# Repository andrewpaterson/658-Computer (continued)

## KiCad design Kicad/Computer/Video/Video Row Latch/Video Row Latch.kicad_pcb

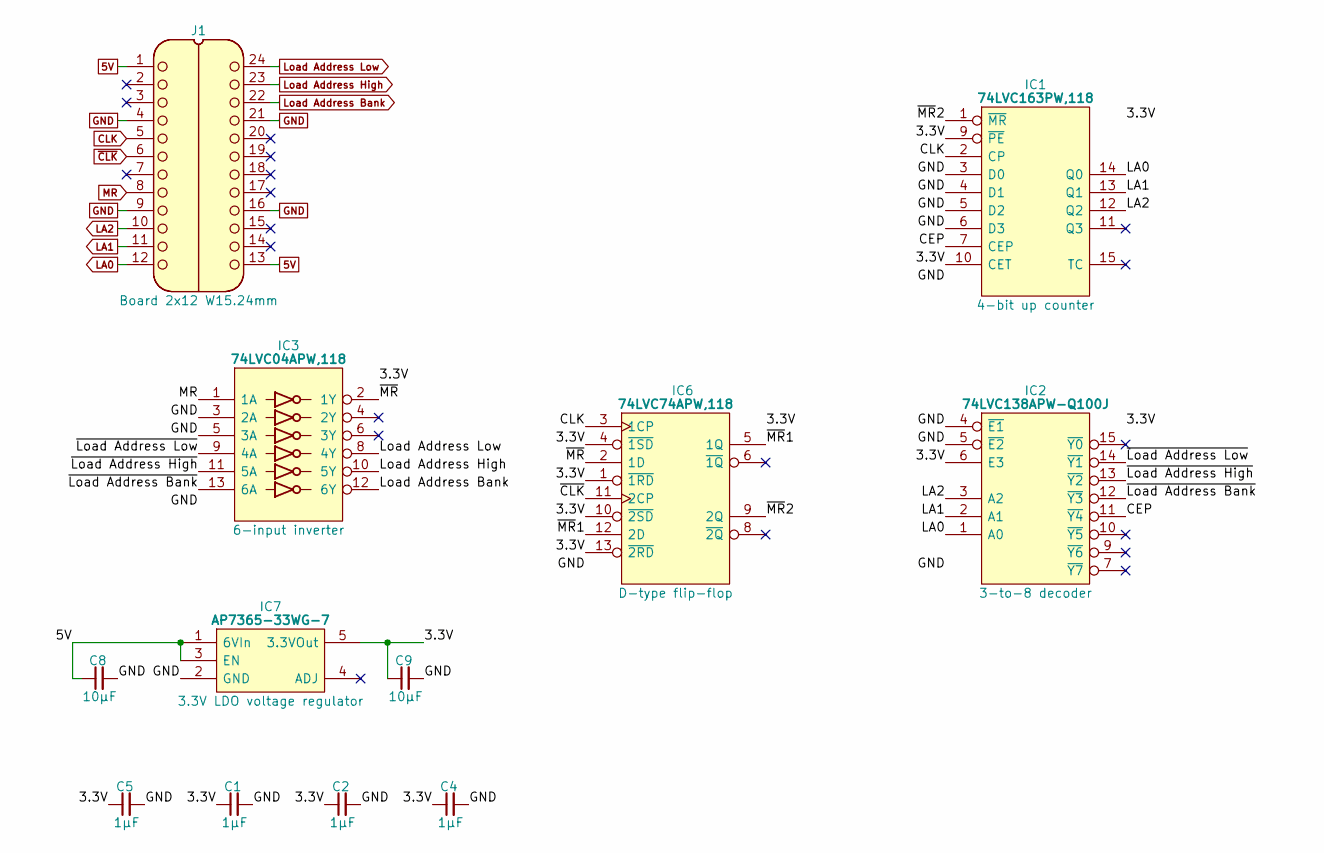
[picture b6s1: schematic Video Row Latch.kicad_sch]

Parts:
C1, C2, C4, C5: 1μF; C_0805
C8, C9: 10μF; C_0805
IC1: 74LVC163PW,118; SOP65P640X110-16N; Mouser Part Number 771-74LVC163PW-T
IC2: 74LVC138APW-Q100J; SOP65P640X110-16N; Mouser Part Number 771-74LVC138APWQ100J
IC3: 74LVC04APW,118; SOP65P640X110-14N; Manufacturer_Part_Number 74LVC04APW,118; Mouser Part Number 771-74LVC04APW-T
IC6: 74LVC74APW,118; SOP65P640X110-14N; Mouser Part Number 771-74LVC74APW-T
IC7: AP7365-33WG-7; SOT95P285X130-5N; Manufacturer_Part_Number AP7365-33WG-7; Mouser Part Number 621-AP7365-33WG-7
J1: Board 2x12 W15.24mm; DIP-24_Board_W15.24mm

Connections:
5V: C8.1, IC7.1 (6VIn), IC7.3 (EN), J1.1, J1.13
/3.3V: C1.1, C2.1, C4.1, C5.1, C9.1, IC1.9 (~PE), IC1.10 (CET), IC1.16 (3V), IC2.6 (E3), IC2.16 (3V), IC3.14 (3V), IC6.1 (~1RD), IC6.4 (~1SD), IC6.10 (~2SD), IC6.13 (~2RD), IC6.14 (3V), IC7.5 (3.3VOut)
/CEP: IC1.7 (CEP), IC2.11 (~Y4)
/~Load Address Bank: IC2.12 (~Y3), IC3.13 (6A)
/~Load Address High: IC2.13 (~Y2), IC3.11 (5A)
/~Load Address Low: IC2.14 (~Y1), IC3.9 (4A)
/~MR: IC3.2 (1Y), IC6.2 (1D)
/~MR1: IC6.5 (1Q), IC6.12 (2D)
/~MR2: IC1.1 (~MR), IC6.9 (2Q)
CLK: IC1.2 (CP), IC6.3 (1CP), J1.5
GND: C1.2, C2.2, C4.2, C5.2, C8.2, C9.2, IC1.3 (D0), IC1.4 (D1), IC1.5 (D2), IC1.6 (D3), IC1.8 (GND), IC2.4 (~E1), IC2.5 (~E2), IC2.8 (GND), IC3.3 (2A), IC3.5 (3A), IC3.7 (GND), IC6.7 (GND), IC7.2 (GND), J1.4, J1.9, J1.16, J1.21
LA0: IC1.14 (Q0), IC2.1 (A0), J1.12
LA1: IC1.13 (Q1), IC2.2 (A1), J1.11
LA2: IC1.12 (Q2), IC2.3 (A2), J1.10
Load Address Bank: IC3.12 (6Y), J1.22
Load Address High: IC3.10 (5Y), J1.23
Load Address Low: IC3.8 (4Y), J1.24
MR: IC3.1 (1A), J1.8
~CLK: IC6.11 (2CP), J1.6

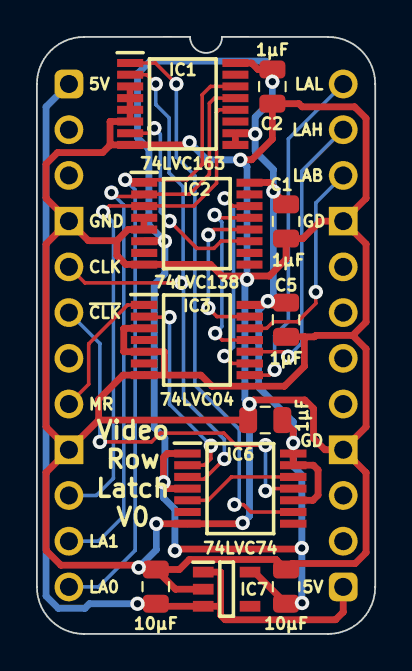
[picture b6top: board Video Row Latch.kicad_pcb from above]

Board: 2 copper layers, 18.8 x 33.2 mm, 12 parts (0 on the bottom side), 19 nets.

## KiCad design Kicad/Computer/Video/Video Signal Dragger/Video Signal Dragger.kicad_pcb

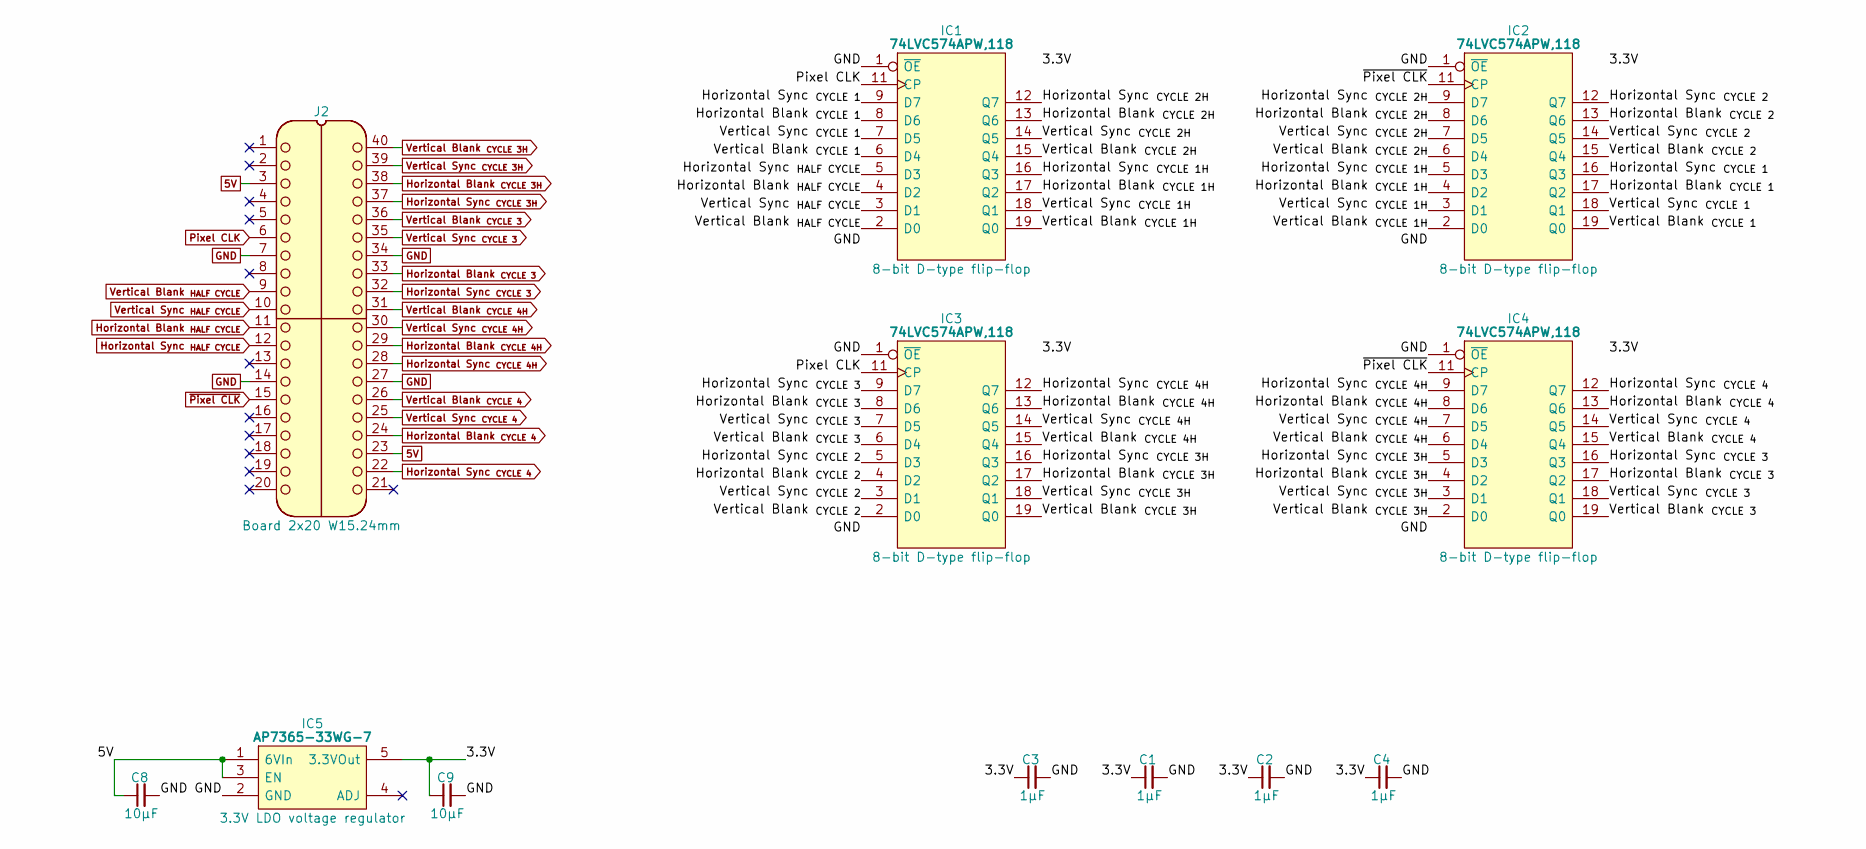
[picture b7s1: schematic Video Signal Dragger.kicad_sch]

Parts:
C1, C2, C3, C4: 1μF; C_0805
C8, C9: 10µF; C_0805
IC1, IC2, IC3, IC4: 74LVC574APW,118; SOP65P640X110-20N; Manufacturer_Part_Number 74LVC574APW,118; Mouser Part Number 771-74LVC574APW-T
IC5: AP7365-33WG-7; SOT95P285X130-5N; Manufacturer_Part_Number AP7365-33WG-7; Mouser Part Number 621-AP7365-33WG-7
J2: Board 2x20 W15.24mm; DIP-40_Board_W15.24mm

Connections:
5V: C8.1, IC5.1 (6VIn), IC5.3 (EN), J2.3, J2.23
/3.3V: C1.1, C2.1, C3.1, C4.1, C9.1, IC1.20 (3V), IC2.20 (3V), IC3.20 (3V), IC4.20 (3V), IC5.5 (3.3VOut)
/Horizontal Blank _{CYCLE 1H}: IC1.17 (Q2), IC2.4 (D2)
/Horizontal Blank _{CYCLE 1}: IC1.8 (D6), IC2.17 (Q2)
/Horizontal Blank _{CYCLE 2H}: IC1.13 (Q6), IC2.8 (D6)
/Horizontal Blank _{CYCLE 2}: IC2.13 (Q6), IC3.4 (D2)
/Horizontal Sync _{CYCLE 1H}: IC1.16 (Q3), IC2.5 (D3)
/Horizontal Sync _{CYCLE 1}: IC1.9 (D7), IC2.16 (Q3)
/Horizontal Sync _{CYCLE 2H}: IC1.12 (Q7), IC2.9 (D7)
/Horizontal Sync _{CYCLE 2}: IC2.12 (Q7), IC3.5 (D3)
/Vertical Blank _{CYCLE 1H}: IC1.19 (Q0), IC2.2 (D0)
/Vertical Blank _{CYCLE 1}: IC1.6 (D4), IC2.19 (Q0)
/Vertical Blank _{CYCLE 2H}: IC1.15 (Q4), IC2.6 (D4)
/Vertical Blank _{CYCLE 2}: IC2.15 (Q4), IC3.2 (D0)
/Vertical Sync _{CYCLE 1H}: IC1.18 (Q1), IC2.3 (D1)
/Vertical Sync _{CYCLE 1}: IC1.7 (D5), IC2.18 (Q1)
/Vertical Sync _{CYCLE 2H}: IC1.14 (Q5), IC2.7 (D5)
/Vertical Sync _{CYCLE 2}: IC2.14 (Q5), IC3.3 (D1)
GND: C1.2, C2.2, C3.2, C4.2, C8.2, C9.2, IC1.1 (~OE), IC1.10 (GND), IC2.1 (~OE), IC2.10 (GND), IC3.1 (~OE), IC3.10 (GND), IC4.1 (~OE), IC4.10 (GND), IC5.2 (GND), J2.7, J2.14, J2.27, J2.34
Horizontal Blank _{CYCLE 3H}: IC3.17 (Q2), IC4.4 (D2), J2.38
Horizontal Blank _{CYCLE 3}: IC3.8 (D6), IC4.17 (Q2), J2.33
Horizontal Blank _{CYCLE 4H}: IC3.13 (Q6), IC4.8 (D6), J2.29
Horizontal Blank _{CYCLE 4}: IC4.13 (Q6), J2.24
Horizontal Blank _{HALF CYCLE}: IC1.4 (D2), J2.11
Horizontal Sync _{CYCLE 3H}: IC3.16 (Q3), IC4.5 (D3), J2.37
Horizontal Sync _{CYCLE 3}: IC3.9 (D7), IC4.16 (Q3), J2.32
Horizontal Sync _{CYCLE 4H}: IC3.12 (Q7), IC4.9 (D7), J2.28
Horizontal Sync _{CYCLE 4}: IC4.12 (Q7), J2.22
Horizontal Sync _{HALF CYCLE}: IC1.5 (D3), J2.12
Pixel CLK: IC1.11 (CP), IC3.11 (CP), J2.6
Vertical Blank _{CYCLE 3H}: IC3.19 (Q0), IC4.2 (D0), J2.40
Vertical Blank _{CYCLE 3}: IC3.6 (D4), IC4.19 (Q0), J2.36
Vertical Blank _{CYCLE 4H}: IC3.15 (Q4), IC4.6 (D4), J2.31
Vertical Blank _{CYCLE 4}: IC4.15 (Q4), J2.26
Vertical Blank _{HALF CYCLE}: IC1.2 (D0), J2.9
Vertical Sync _{CYCLE 3H}: IC3.18 (Q1), IC4.3 (D1), J2.39
Vertical Sync _{CYCLE 3}: IC3.7 (D5), IC4.18 (Q1), J2.35
Vertical Sync _{CYCLE 4H}: IC3.14 (Q5), IC4.7 (D5), J2.30
Vertical Sync _{CYCLE 4}: IC4.14 (Q5), J2.25
Vertical Sync _{HALF CYCLE}: IC1.3 (D1), J2.10
~Pixel CLK: IC2.11 (CP), IC4.11 (CP), J2.15

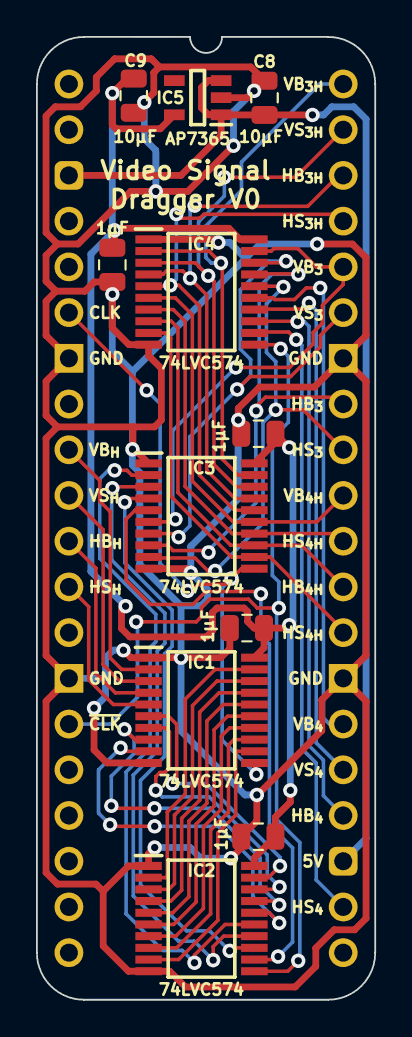
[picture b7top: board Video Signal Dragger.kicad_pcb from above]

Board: 2 copper layers, 18.8 x 53.5 mm, 12 parts (0 on the bottom side), 41 nets.

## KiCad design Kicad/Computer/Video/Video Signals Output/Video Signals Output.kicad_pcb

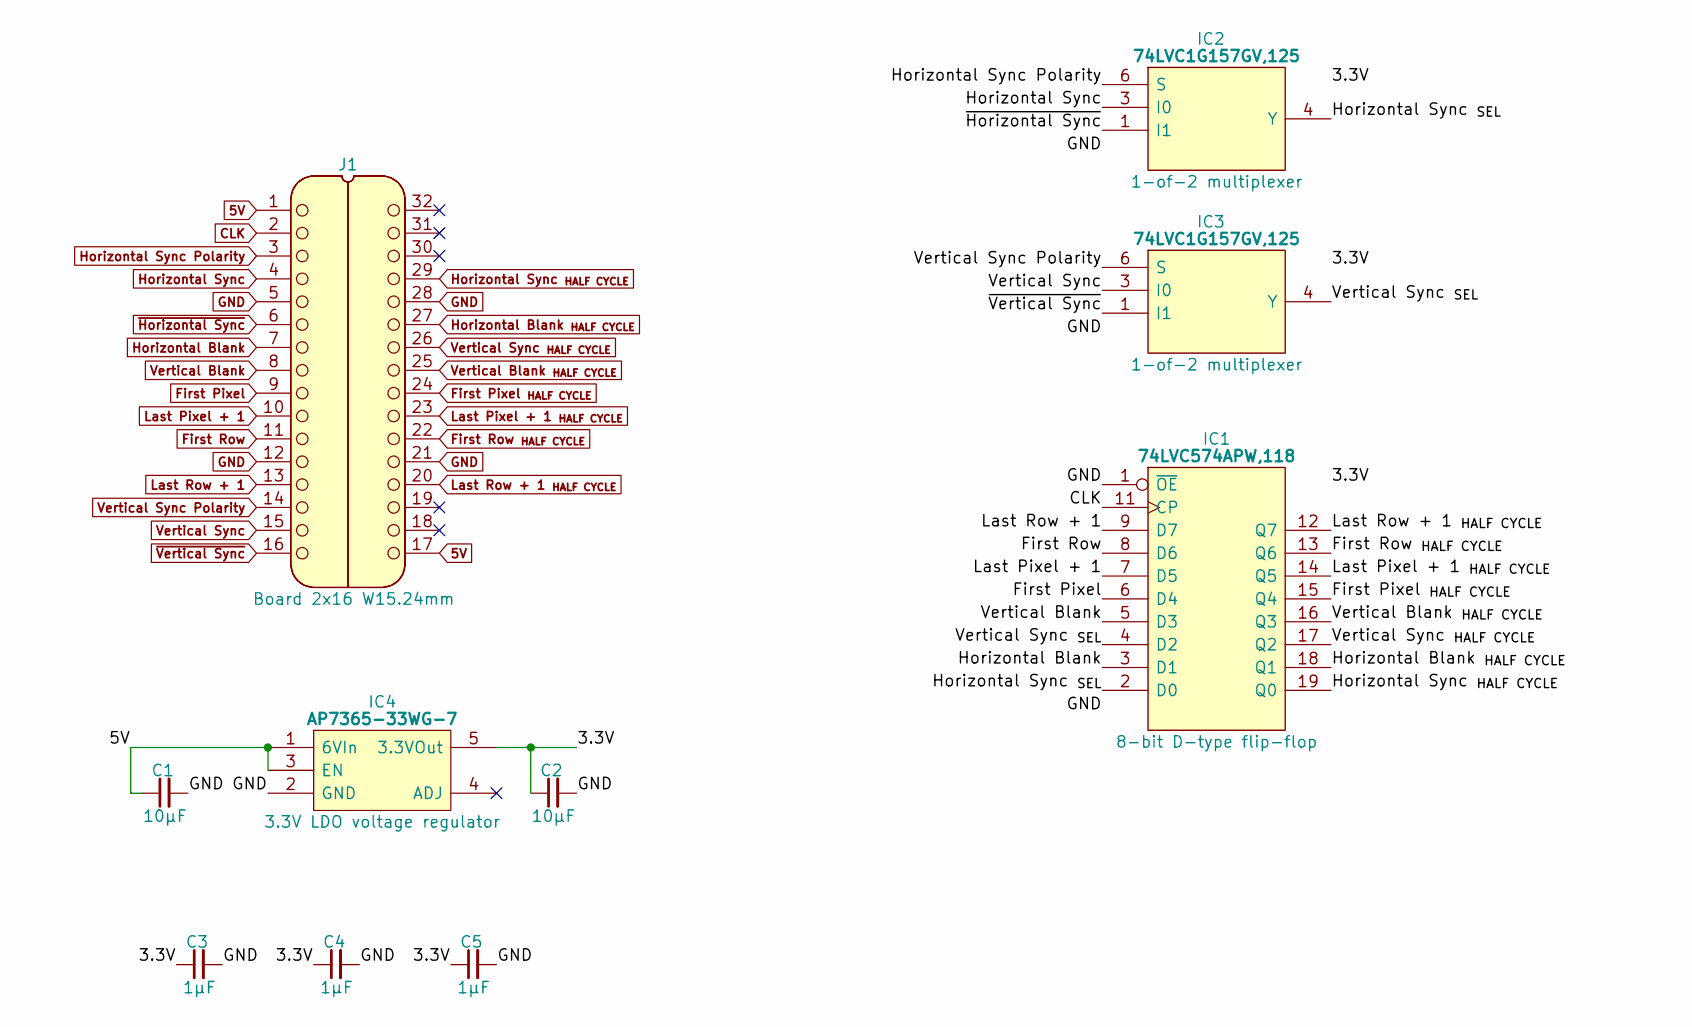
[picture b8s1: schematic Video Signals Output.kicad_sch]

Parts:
C1, C2: 10µF; C_0805
C3, C4, C5: 1μF; C_0805
IC1: 74LVC574APW,118; SOP65P640X110-20N; Manufacturer_Part_Number 74LVC574APW,118; Mouser Part Number 771-74LVC574APW-T
IC2, IC3: 74LVC1G157GV,125; 74LVC1G157GV125; Manufacturer_Part_Number 74LVC1G157GV,125; Mouser Part Number 771-74LVC1G157GV-G
IC4: AP7365-33WG-7; SOT95P285X130-5N; Manufacturer_Part_Number AP7365-33WG-7; Mouser Part Number 621-AP7365-33WG-7
J1: Board 2x16 W15.24mm; DIP-32_Board_W15.24mm

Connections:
5V: C1.1, IC4.1 (6VIn), IC4.3 (EN), J1.1, J1.17
/3.3V: C2.1, C3.1, C4.1, C5.1, IC1.20 (3V), IC2.5 (3V), IC3.5 (3V), IC4.5 (3.3VOut)
/Horizontal Sync _{SEL}: IC1.2 (D0), IC2.4 (Y)
/Vertical Sync _{SEL}: IC1.4 (D2), IC3.4 (Y)
CLK: IC1.11 (CP), J1.2
First Pixel: IC1.6 (D4), J1.9
First Pixel _{HALF CYCLE}: IC1.15 (Q4), J1.24
First Row: IC1.8 (D6), J1.11
First Row _{HALF CYCLE}: IC1.13 (Q6), J1.22
GND: C1.2, C2.2, C3.2, C4.2, C5.2, IC1.1 (~OE), IC1.10 (GND), IC2.2 (GND), IC3.2 (GND), IC4.2 (GND), J1.5, J1.12, J1.21, J1.28
Horizontal Blank: IC1.3 (D1), J1.7
Horizontal Blank _{HALF CYCLE}: IC1.18 (Q1), J1.27
Horizontal Sync: IC2.3 (I0), J1.4
Horizontal Sync Polarity: IC2.6 (S), J1.3
Horizontal Sync _{HALF CYCLE}: IC1.19 (Q0), J1.29
Last Pixel + 1: IC1.7 (D5), J1.10
Last Pixel + 1 _{HALF CYCLE}: IC1.14 (Q5), J1.23
Last Row + 1: IC1.9 (D7), J1.13
Last Row + 1 _{HALF CYCLE}: IC1.12 (Q7), J1.20
Vertical Blank: IC1.5 (D3), J1.8
Vertical Blank _{HALF CYCLE}: IC1.16 (Q3), J1.25
Vertical Sync: IC3.3 (I0), J1.15
Vertical Sync Polarity: IC3.6 (S), J1.14
Vertical Sync _{HALF CYCLE}: IC1.17 (Q2), J1.26
~Horizontal Sync: IC2.1 (I1), J1.6
~Vertical Sync: IC3.1 (I1), J1.16

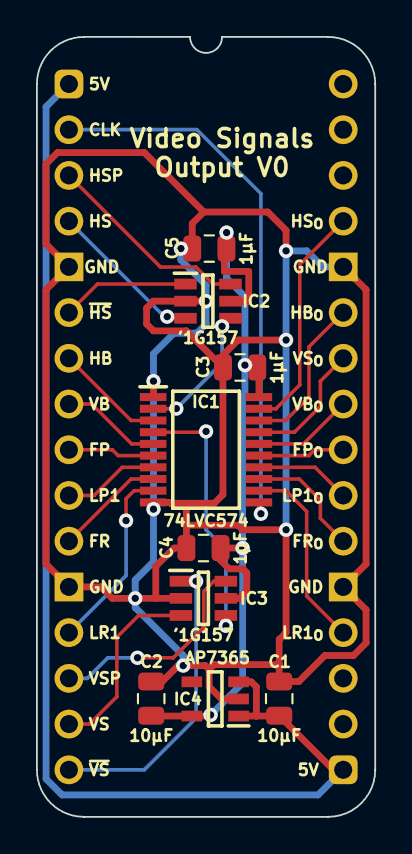
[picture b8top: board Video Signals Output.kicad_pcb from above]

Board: 2 copper layers, 18.8 x 43.3 mm, 10 parts (0 on the bottom side), 26 nets.
